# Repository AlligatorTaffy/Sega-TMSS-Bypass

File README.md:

# Sega TMSS Bypass
 
This bypasses the "PRODUCED BY SEGA" Trademark that is burned into the bootrom of later model Sega Genesis.  I found the schematics online years ago and then created the schematics and board in CadSoft Eagle.

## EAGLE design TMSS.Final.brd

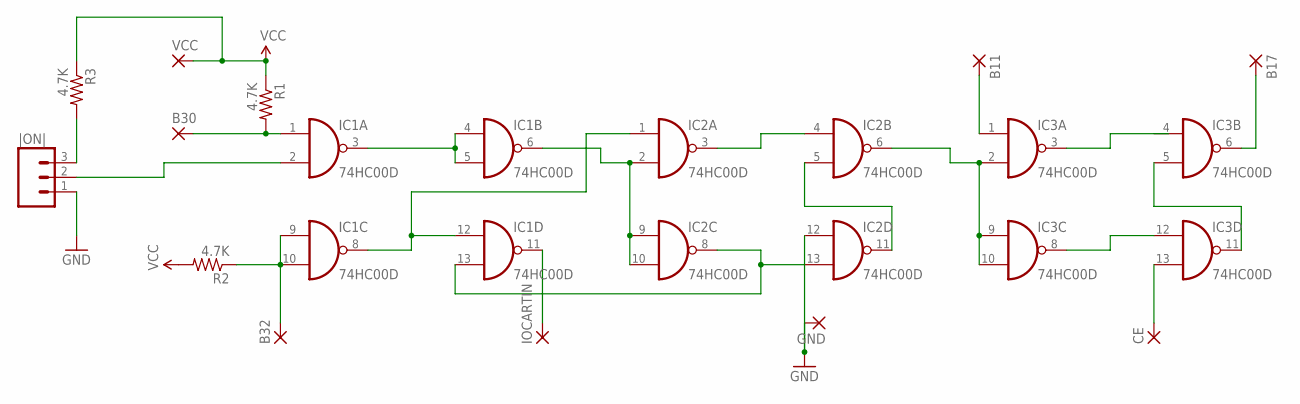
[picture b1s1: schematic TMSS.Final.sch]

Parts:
B11, B17, B30, B32: 1,6/0,9
CE: 1,6/0,9
GND: 1,6/0,9
IC1, IC2, IC3: 74HC00D; SO14
IOCARTIN: 1,6/0,9
R1, R2, R3: 4.7K; 0805
VCC: 1,6/0,9
|ON|: M03PTH; 1X03

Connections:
GND: GND.1, IC1.7 (GND), IC2.7 (GND), IC2.12 (I0), IC3.7 (GND), |ON|.1
unnamed: IC1.3 (O), IC1.4 (I0), IC1.5 (I1)
unnamed: B32.1, IC1.9 (I0), IC1.10 (I1), R2.1
unnamed: IC1.8 (O), IC1.12 (I0), IC2.1 (I0)
unnamed: IC1.13 (I1), IC2.8 (O), IC2.13 (I1)
unnamed: IC1.6 (O), IC2.2 (I1), IC2.9 (I0), IC2.10 (I1)
unnamed: IC2.3 (O), IC2.4 (I0)
unnamed: IC2.5 (I1), IC2.11 (O)
unnamed: IC2.6 (O), IC3.2 (I1), IC3.9 (I0), IC3.10 (I1)
unnamed: IC3.8 (O), IC3.12 (I0)
unnamed: IC3.5 (I1), IC3.11 (O)
unnamed: B30.1, IC1.1 (I0), R1.2
unnamed: IC1.11 (O), IOCARTIN.1
unnamed: B11.1, IC3.1 (I0)
unnamed: B17.1, IC3.6 (O)
unnamed: CE.1, IC3.13 (I1)
unnamed: IC1.2 (I1), |ON|.2
unnamed: R3.2, |ON|.3
VCC: IC1.14 (VCC), IC2.14 (VCC), IC3.14 (VCC), R1.1, R2.2, R3.1, VCC.1

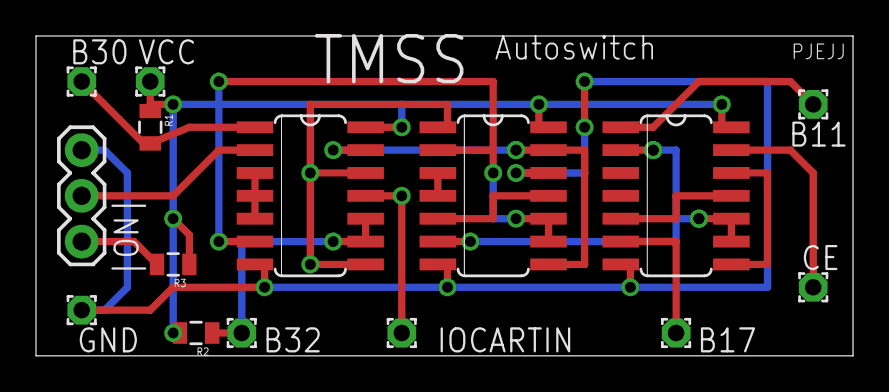
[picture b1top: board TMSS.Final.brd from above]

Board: 2 copper layers, 45.4 x 17.8 mm, 15 parts (0 on the bottom side), 19 nets.

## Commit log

2023-05-29 Migrate to GitHub

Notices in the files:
parts and their libraries:
SparkFun-Resistors: Licensing: CC v3.0 Share-Alike You are welcome to use this library for commercial purposes.
